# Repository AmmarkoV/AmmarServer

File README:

A lightweight extendable barebones HTTP server for linux
Please see the wiki for more info on whats going on in this repository : )
https://github.com/AmmarkoV/AmmarServer/wiki

One of the most basic philosophies behind this is to try to add as much functionality possible in a reusable way *WITHOUT* overly increasing loc and dependencies.. The biggest recent improvements have been actually trying to merge common functionality and reducing loc. 

------------------------------------------------------------------ 

The projects build dependencies are the gcc compiler , pthreads , cmake and pretty basic things 
so if you issue sudo apt-get install build-essential  ( assuming a Debian/Ubuntu based system ) you should be able to compile it without problems..

Newer versions also support compression , so you might want to also apt-get install liblzma-dev if you enable ENABLE_COMPRESSION at server_configuration.h
MyURL needs libjpeg in order to serve captchas , so to add it sudo apt-get install libjpeg-dev

To perform a compilation you just need to issue 
mkdir build 
cd build 
cmake ..
make

This should try to compile all of the project files which you can then run using the scripts listed in the list below 

To update your version of the project you can use the provided script that updates directly from github
It will remove any changes you have made to any of the files in the repository   
./update_from_git from the root directory 

------------------------------------------------------------------

This Repository contains :

-  The AmmarServer library with which you can build your own highly optimized 
and fully customizable web service..

-  A template for starting to build your own webserver which is very well documented
   https://github.com/AmmarkoV/AmmarServer/blob/master/src/Services/SimpleTemplate/main.c
   You can run it by issuing ./run_simpleTemplate from root directory 

-  A simple (but extensible) webserver demo showcasing some dynamic pages
   https://github.com/AmmarkoV/AmmarServer/blob/master/src/Services/main.c
   You can run it by issuing ./run_ammarserver from root directory 

-  A URL Shortner service like tinyurl , bitly , goo.gl etc..
   https://github.com/AmmarkoV/AmmarServer/tree/master/src/Services/MyURL/
   You can run it by issuing ./run_myurl from root directory 

-  A File Uploader service based on MyLoader , currently under construction..
   https://github.com/AmmarkoV/AmmarServer/tree/master/src/Services/MyLoader/
   You can run it by issuing ./run_myloader from root directory 

-  A Web Service that allows location sharing ..
   https://github.com/AmmarkoV/AmmarServer/tree/master/src/Services/GeoPosShare/
   You can run it by issuing ./run_geoposshare from root directory 

-  A Remote Desktop Sharing Web Service that allows controlling your linux desktop through a web browser  ..
   https://github.com/AmmarkoV/AmmarServer/tree/master/src/Services/MyRemoteDesktop/
   You can run it by issuing ./run_myremotedesktop from root directory 

-  A Youtube like clone ..
   https://github.com/AmmarkoV/AmmarServer/tree/master/src/Services/MyTube/
   You can run it by issuing ./run_mytube from root directory 

-  A Blog engine that can use Wordpress skins..
   https://github.com/AmmarkoV/AmmarServer/tree/master/src/Services/MyBlog/
   You can run it by issuing ./run_myblog from root directory 

-  A 4chan like  engine for hosting a small image board , currently under construction..
   https://github.com/AmmarkoV/AmmarServer/tree/master/src/Services/HabChan/
   You can run it by issuing ./run_habchan from root directory 

------------------------------------------------------------------

AmmarServer is also an integral part , providing network connectivity and used in the following projects :
V4L2ToHTTP       : https://github.com/AmmarkoV/V4L2ToHTTP/
RoboVision       : https://github.com/AmmarkoV/RoboVision/ 
FlashySlideshows : https://github.com/AmmarkoV/FlashySlideshows/
RGBDAcquisition  : https://github.com/AmmarkoV/RGBDAcquisition

This project has also been successfully deployed as a means to control embedded platforms like Robots
For Hobbit EU Project : https://www.youtube.com/watch?v=41_8ktacxt8 , http://hobbit.acin.tuwien.ac.at/
For GuarddoG Robot    : https://www.youtube.com/watch?v=61GGKFbzG7I , https://github.com/AmmarkoV/RoboVision/blob/master/Documentation/GuarDDoG_RoboVision.pdf
For Softbank NAO Robot Realtime Bridge : https://www.youtube.com/watch?v=axfKwyVTRuA

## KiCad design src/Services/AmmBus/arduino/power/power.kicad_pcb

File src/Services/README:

This directory contains all the services someone can use with AmmarServer
A developer should probably copy the simpletemplate directory and create his or her project here so that things are kept tidy and neat.

Among Services that get shipped with AmmarServer are  : 

MyURL 
MyLoader
GeoPosShare

The libraries which these projects depend upon should be on the parent directory of this Services dir

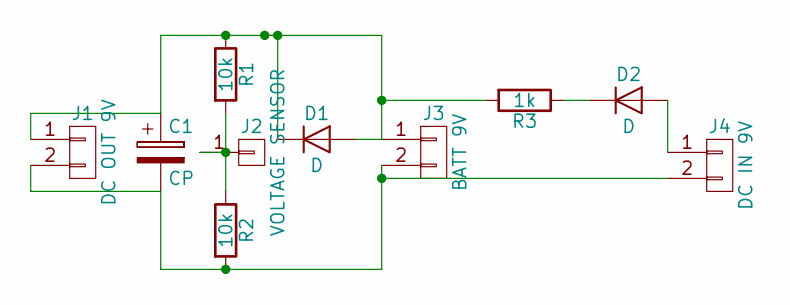
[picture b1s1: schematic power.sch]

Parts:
C1: CP; CP_Elec_6.3x7.7
D1, D2: D; D_DO-41_SOD81_P7.62mm_Horizontal
J1: DC OUT 9V; Pin_Header_Angled_1x02_Pitch2.00mm
J2: VOLTAGE SENSOR; Pin_Header_Angled_1x01_Pitch2.00mm
J3: BATT 9V; Pin_Header_Angled_1x02_Pitch2.00mm
J4: DC IN 9V; Pin_Header_Angled_1x02_Pitch2.00mm
R1, R2: 10k; R_1210_HandSoldering
R3: 1k; R_1210_HandSoldering

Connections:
unnamed: C1.1, D1.1 (K), D1.2 (A), J1.1, J3.1, R1.1, R3.2
unnamed: C1.2, J1.2, J3.2, J4.2, R2.2
unnamed: D2.1 (K), R3.1
unnamed: D2.2 (A), J4.1
unnamed: J2.1, R1.2, R2.1

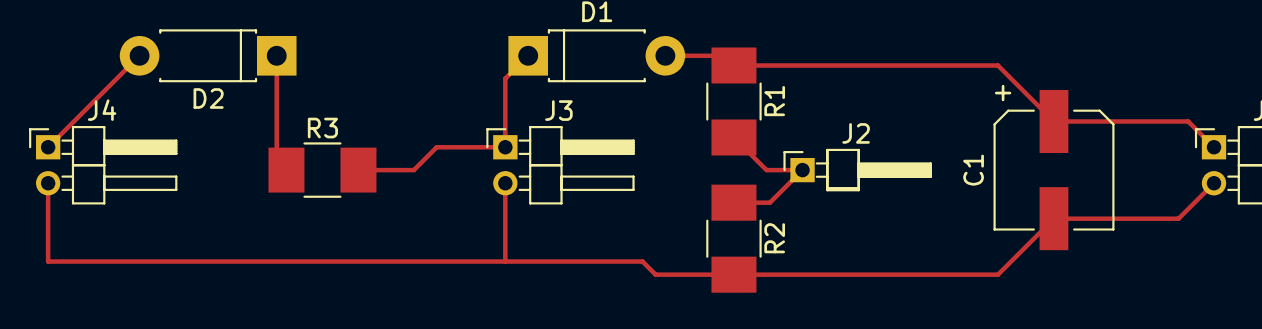
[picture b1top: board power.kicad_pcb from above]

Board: 2 copper layers, 10 parts (0 on the bottom side), 5 nets.

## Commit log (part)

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2018-08-20 plans to split the serial Communication code..
2018-08-21 rearranging ammBus waterchip
2018-08-21 rearranging code to clean it up..
2018-08-21 yet more separation..
2018-08-21 refactoring arduino code..
2018-08-22 improving serial USB communication , allowing to set the time from serial..
2018-08-22 more improvements encountering some strange bugs in DS3231 time formatting..
2018-08-22 small improvements..
2018-08-23 more refactoring at 20/32k
2018-08-23 more work on ammbus..
2018-08-23 getting rid of public variables..
2018-09-05 adding a power module schematic ( my first kicad project :) )
2018-09-14 adding a nano headless board target..
2018-09-16 making a new simpler ethernet based ammbus..
2018-09-16 restructuring..
2018-09-16 adding an i2c scan utility for DS3231 clock..
2018-09-16 adding a seperate ethernet file..
2018-09-16 using the same codebase for the nano as for the lcd version..
2018-11-01 AmmMessages producing output compatible with C++
2018-11-26 filtering paths..
2018-11-26 also including a version number in message generator..
2018-11-26 different replaceChar implementation..
2018-11-28 generator skipping all path..
2018-11-28 various small additions to AmmMessages..
2018-11-30 added switchable ammmessage testing..
2018-12-05 adding support for w8ing until a message is consumed..
2018-12-16 adding a new project for animal house ammbus..
2018-12-19 giving the animalhouse the full ammbus stack..
2018-12-19 reducing footprint 20866 bytes (64%) of program storage space 1466 bytes (71%) of dynamic memory
2018-12-19 now to add temperature logging..
2018-12-19 adding a way to log temperatures..
2019-01-04 adding a push service service..
2019-01-08 adding push service to scripts..
2019-01-08 more work on the currently incredibly simple push service..
2019-01-09 adding a CSVParser so that it can parse the authorization list needed for APushService..
2019-01-10 more work on the CSV code..
2019-01-13 adding a new seperater arduino sketch for the temperature sensors..
2019-01-13 animalNano will be the final incarnation of the thermostat..
2019-01-13 more work on animal house thermostat and push service..
2019-01-13 now using my server as default..
2019-01-13 added logging..
2019-01-14 flashed final configuration ( IPs etc ), better connection handling..
2019-01-14 fixed the animalNano ethernet loop..
2019-01-15 ready for deployment..
2019-01-15 APushService is becoming beautiful :)
2019-01-15 many changes ...
2019-01-15 everything is shaping up..
2019-01-15 trying to plot temperatures but I think I will call it a day..
2019-01-16 better code structure enabling e-mails for alerts and added a 20 min cut-off
2019-01-16 changed frequency to 1hr
2019-01-17 more stuff on APushService..
2019-01-18 now using local time for user data..
2019-01-18 adding systemd service to startup server..
2019-01-18 rearranged installation script..
2019-01-18 reduced ammarserver console output since systemd logs on syslog and it clutters a lot..
2019-01-18 further reducing spam..
2019-01-18 less console output , single gnuplot scripts..
2019-01-18 added dynamic gnuplots through popen to apushservice and it looks great..!
2019-01-18 now only plotting recent readings..
2019-01-20 cleaned up embedded stuff, now using ESP-01 for wifi temperature controller..
2019-01-20 adding new DHT lib just for ESP maybe this works..
2019-01-21 ESP-01 DHT11 Temperature sensor working..
2019-01-22 more information on devices when doing checks..
2019-01-25 some improvements on ESP-01 code..
2019-01-25 ammbusNano also working..
2019-01-25 renamed device..
2019-01-27 adding static IP code to animalESP
2019-02-02 apush service gnuplot graphs are now cached and do not need to be spammed
2019-02-03 preparing APushService to parse csv configuration files..
2019-02-03 slowly adding configuration csv files for apushservice..
2019-02-11 rearranged incorrect request counting in ESP01 sensors.
2019-02-13 banlist updated with ips that try to attack my server..
2019-03-06 added -D_FORTIFY_SOURCE=2 flag to all executables..
2019-03-06 corrected all warnings on gcc 6.5.0
2019-03-07 rephrased mailed message a little..
2019-03-07 now filtering temperatures internally..
2019-03-26 doubled plot samples
2019-04-11 adjusted temperature limits..
2019-06-10 added pressure sensor..
2019-06-11 sensor now operating at 250.0Hz
2019-07-30 adding kinova code so that it is commited somewhere ( requires https://github.com/fawkesrobotics/libkindrv )
2020-05-03 fixed forgotten memory deallocation on a print statement..
2020-05-22 ammbus now supports an exclusive activation and set to use /dev/ttyUSB0 by default..
2020-07-05 Changed header ends to /r/n/r/n to fix https://github.com/AmmarkoV/AmmarServer/issues/26
2020-10-26 adding a command line argument to change serving directory..
2020-10-29 increased resolution of myremotedesktop..
2020-10-30 some small improvements on my remote desktop ammarserver service..
2020-10-30 added crop start paremeters
2020-11-02 added a webXR example for remote desktop..
2020-11-02 my demo works however webxr requires https...
2020-11-02 ... darn https
2020-11-02 added a script to create an SSL certificate..
2020-11-02 staging openssl stuff
2020-11-24 myremote desktop now uses a mutex to protect XCB/XWD calls that are not inherently thread safe
2021-05-24 updated ethernet code for newer arduino IDE
2021-05-26 adding a dummy ESP32 script..
2021-05-28 adding fritzing schematic..
2021-05-31 last second fixes..
2021-08-19 added Static IP mode, fixed initialization bug on ESP32 watering system..
2021-08-19 some more small fixes..
2021-08-23 add auto-reconnect ESP32 feature on bad connections
2021-08-25 adding UI switches for timing..
2021-08-30 ESP32 restarts if 5 wifi reconnection fails ..
2021-08-30 check for wifi drops faster..
2021-08-31 more wifi checks..
2021-10-25 making the POST multipart/form-data client work..
2021-10-26 added a POST multipart streamer using curllib..
2021-10-26 yey POST multipart works ( at last )
2021-10-28 content length is capitalized like apache now..
2021-10-28 fixed file recv
2021-10-29 small cleanup..
2022-04-14 add new address..
2022-04-14 compatibility with newer ESP compiler/ gnuplots have a fixed size..
2022-04-14 adding some delay to make sure gnuplot has completed its work..
2022-04-15 log log errors when saving temperatures..
2022-04-15 slight configuration tuning (since I've been testing the code on a RPI4)
2022-04-18 some final memos
2022-04-18 not showing humidity reading attempting to make it easier for the RPI
2022-04-18 smaller plot..
2022-05-09 added very old css file
2022-05-09 more old icons..
2022-05-22 updated esp code to make it more stable..
2022-06-03 using the newest example on espressif github for handling wifi latency
2022-06-03 using same max timeout as espressif sample https://github.com/espressif/arduino-esp32/blob/master/libraries/WiFi/examples/WiFiClient/WiFiClient.ino#L76
2022-07-16 my remote desktop stuff
2022-09-17 add an image generation front-end
2022-09-17 almost ready image generation front-end
2022-09-18 proper handling on AmmServer_FreeMemoryHandler
2022-09-18 various small fixes
2022-09-29 adding upload for img2img
2023-02-20 added programmable stablediffusion strength
2023-06-22 now controlling seed..
2024-05-22 add a codec string recognizer for other applications
2024-08-16 small fixes..
2024-08-19 cumulative changes :S
2024-08-19 updated jpginput (hope I didnt break anything :P)
2025-01-30 image generator configurable port
2025-03-16 add a script to plot temp data
2025-03-16 switch to msmtp instead of ssmtp
2025-06-01 playing with V4L2 after I don't know how many years
2025-06-01 updated jpg code
2026-03-31 add SSL
2026-03-31 more ssl code..
2026-04-01 SSL working..
2026-06-07 fix POST bug..
